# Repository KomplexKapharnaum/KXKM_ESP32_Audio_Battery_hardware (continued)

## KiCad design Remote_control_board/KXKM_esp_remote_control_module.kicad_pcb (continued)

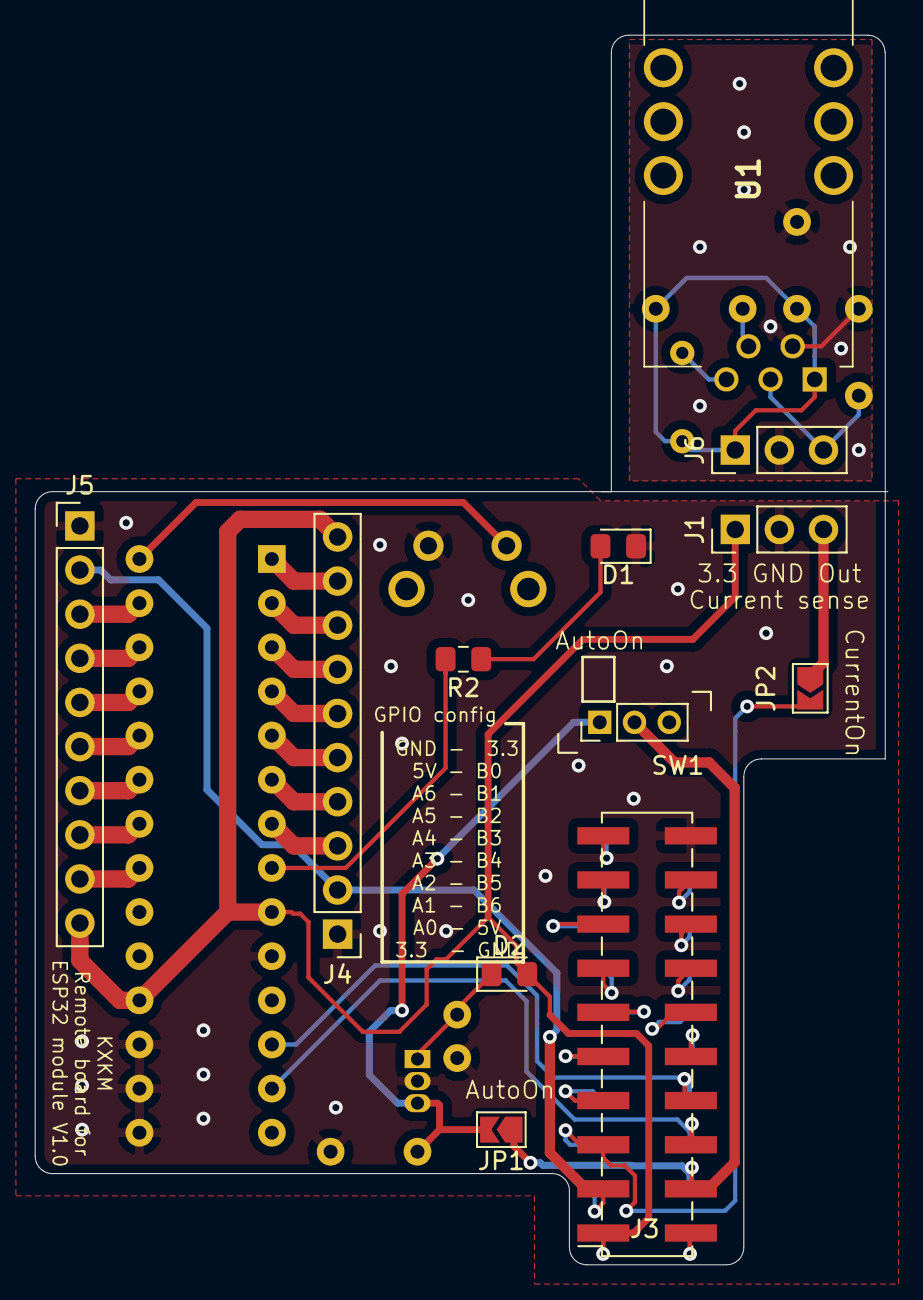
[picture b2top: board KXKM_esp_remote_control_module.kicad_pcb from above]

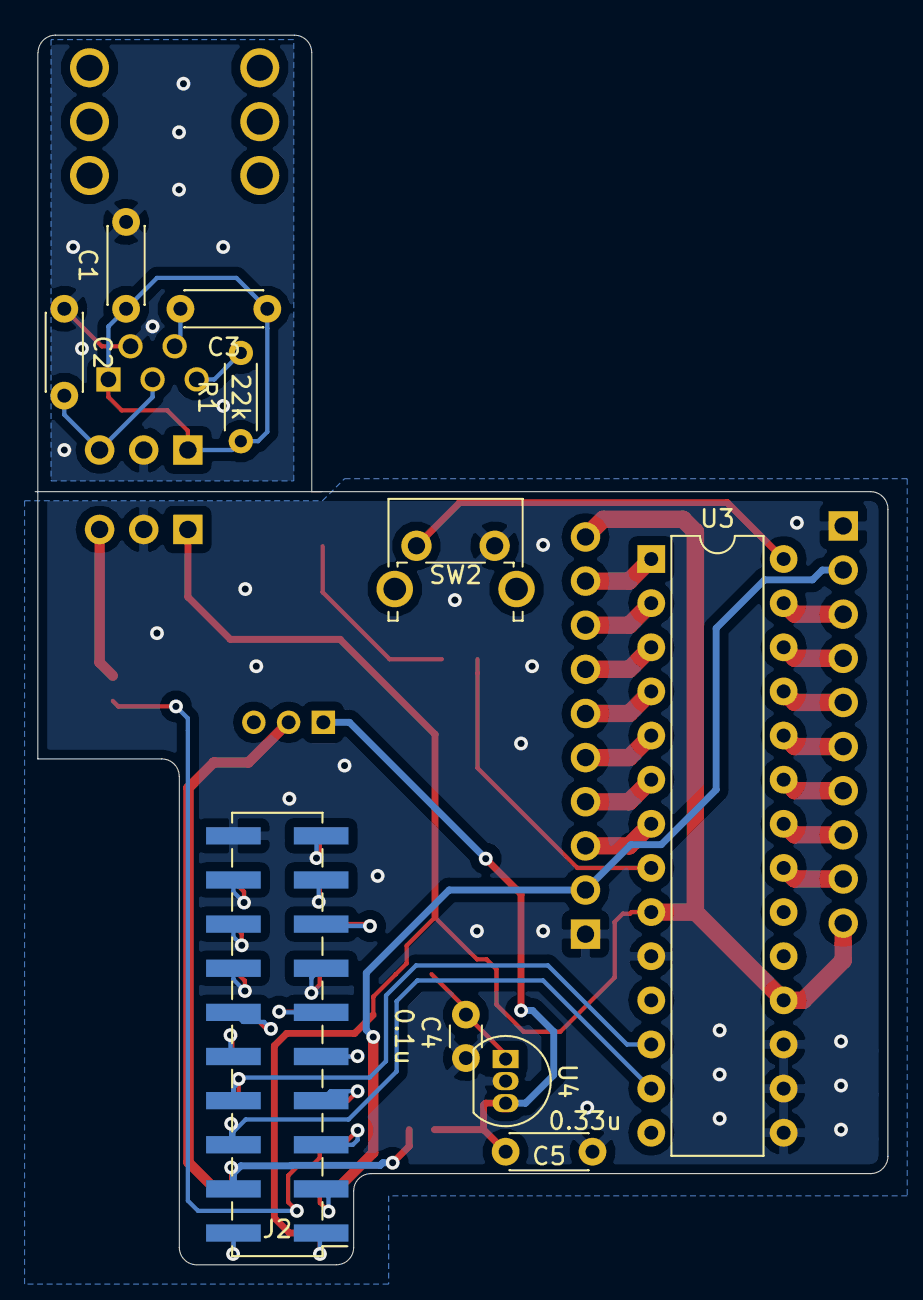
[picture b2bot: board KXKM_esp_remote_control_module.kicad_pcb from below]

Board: 2 copper layers, 48.9 x 70.8 mm, 22 parts (10 on the bottom side), 45 nets.

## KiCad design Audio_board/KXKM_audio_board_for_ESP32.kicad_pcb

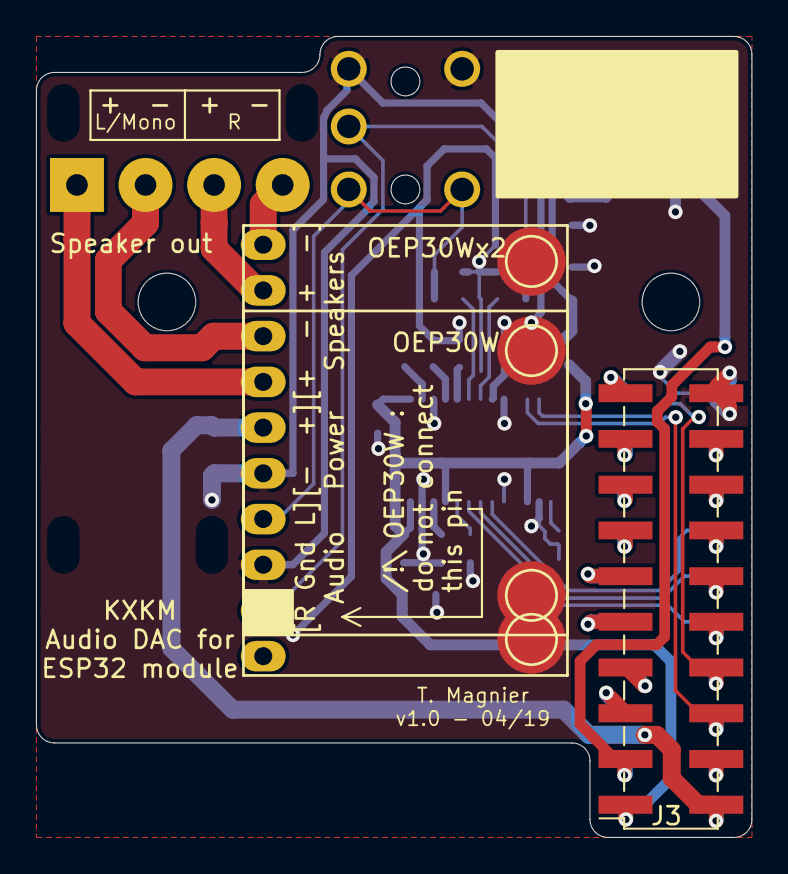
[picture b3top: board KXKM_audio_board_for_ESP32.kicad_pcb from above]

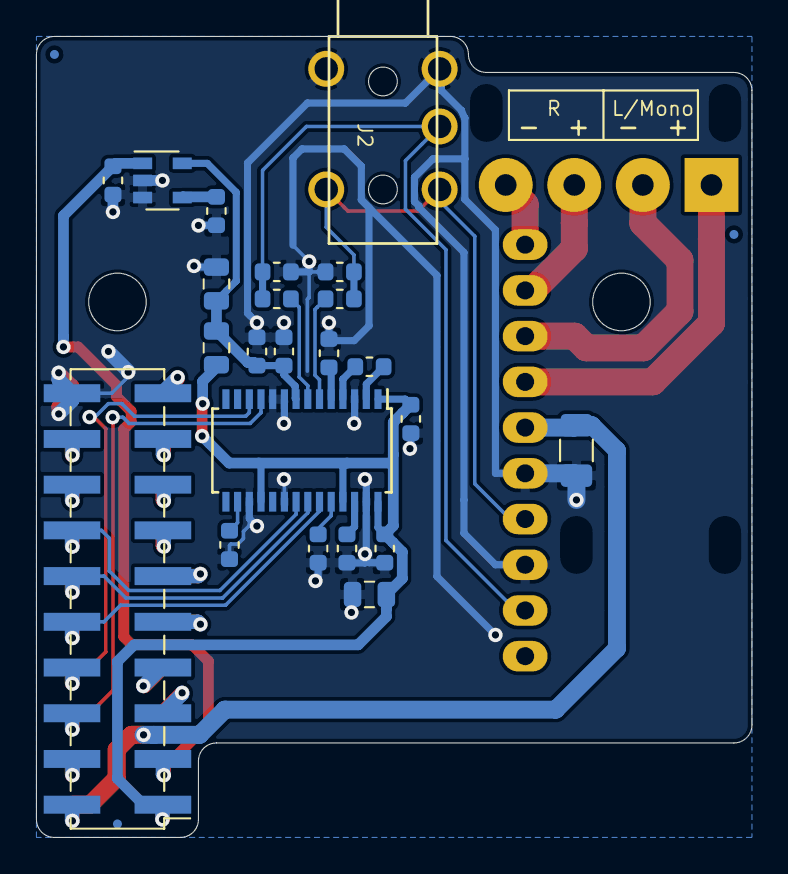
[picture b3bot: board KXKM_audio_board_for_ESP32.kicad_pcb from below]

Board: 2 copper layers, 39.8 x 44.5 mm, 32 parts (26 on the bottom side), 36 nets.

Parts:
C1, C6, C7, C8, C11: 0.1uF; C_0603_1608Metric
C2: 10nF; C_0603_1608Metric
C3, C5: 10uF; C_0805_2012Metric
C4: 1uF; C_0603_1608Metric
C9, C10: 2.2uF/25V; C_0603_1608Metric
C12, C13: 2.2nF/C0G; C_0603_1608Metric
C14: 10uF/50V; C_1206_3216Metric
FB1: Ferrite/60R/3A; L_0805_2012Metric
FID1, FID2, FID3: Fiducial; Fiducial_0.5mm_Mask1mm
H1, H2: MountingHole; MountingHole_3.2mm_M3
J1: Conn_02x10_Odd_Even; PinHeader_2x10_P2.54mm_Vertical_SMD
J2: AudioJack2_Ground; Jack_3.5mm_stereo_PJ-313D
J3: Conn_02x10_Odd_Even; PinSocket_2x10_P2.54mm_Vertical_SMD
J4: Conn_01x04; SolderWirePad_1x04_P3.81mm_Drill1.2mm
R1, R2: 470R/1%; R_0603_1608Metric
R3, R4: 10k; R_0603_1608Metric
U1: DNP/TPS79133DBVR; SOT-23-5
U2: PCM5121; TSSOP-28_4.4x9.7mm_P0.65mm
U3: Audio_amp_OEP30W
U4: Audio_amp_OEP30Wx2

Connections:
+3.3VA: C4.1, C5.1, C7.1, FB1.1, U1.5, U2.8
+3V3: C3.1, C6.1, C8.1, FB1.2, J1.1, J3.1, U2.1, U2.18, U2.25, U2.28
+BATT: J1.4, J3.4
+VSW: C14.1, J1.2, J3.2, U4.5
/ADC: J1.5, J3.5
/Audio/ADDR_1: R3.1, U2.24
/Audio/ADDR_2: R4.1, U2.16
/Audio/AUDIO_L: C13.1, J2.T, R1.1, U4.7
/Audio/AUDIO_R: C12.1, J2.S, R2.1, U4.9
/DMX_DE: J1.15, J3.15
/DMX_DI: J1.17, J3.17
/DMX_RO: J1.19, J3.19
/I2C_SCL: J1.8, J3.8, U2.12
/I2C_SDA: J1.6, J3.6, U2.11
/I2S_BCK: J1.14, J3.14, U2.21
/I2S_DATA: J1.12, J3.12, U2.22
/I2S_LRCK: J1.10, J3.10, U2.23
/LED_D1: J1.16, J3.16
/LED_D2: J1.18, J3.18
/SPI_CS: J1.13, J3.13
/SPI_MISO: J1.9, J3.9
/SPI_MOSI: J1.11, J3.11
/SPI_SCK: J1.7, J3.7
GND: C1.1, C2.1, C3.2, C4.2, C5.2, C6.2, C7.2, C8.2, C10.2, C11.2, C12.2, C13.2, C14.2, J1.20, J2.G, J3.20, R3.2, R4.2, U1.2, U1.3, U2.3, U2.9, U2.10, U2.17, U2.20, U2.27, U3.4, U4.6, U4.8
unnamed: C2.2, U1.4
unnamed: C9.1, U2.2
unnamed: C9.2, U2.4
unnamed: C10.1, U2.5
unnamed: C11.1, U2.26
unnamed: J4.1, U4.4
unnamed: J4.2, U4.3
unnamed: J4.3, U4.2
unnamed: J4.4, U4.1
unnamed: R1.2, U2.6
unnamed: R2.2, U2.7
VBUS: C1.2, J1.3, J3.3, U1.1

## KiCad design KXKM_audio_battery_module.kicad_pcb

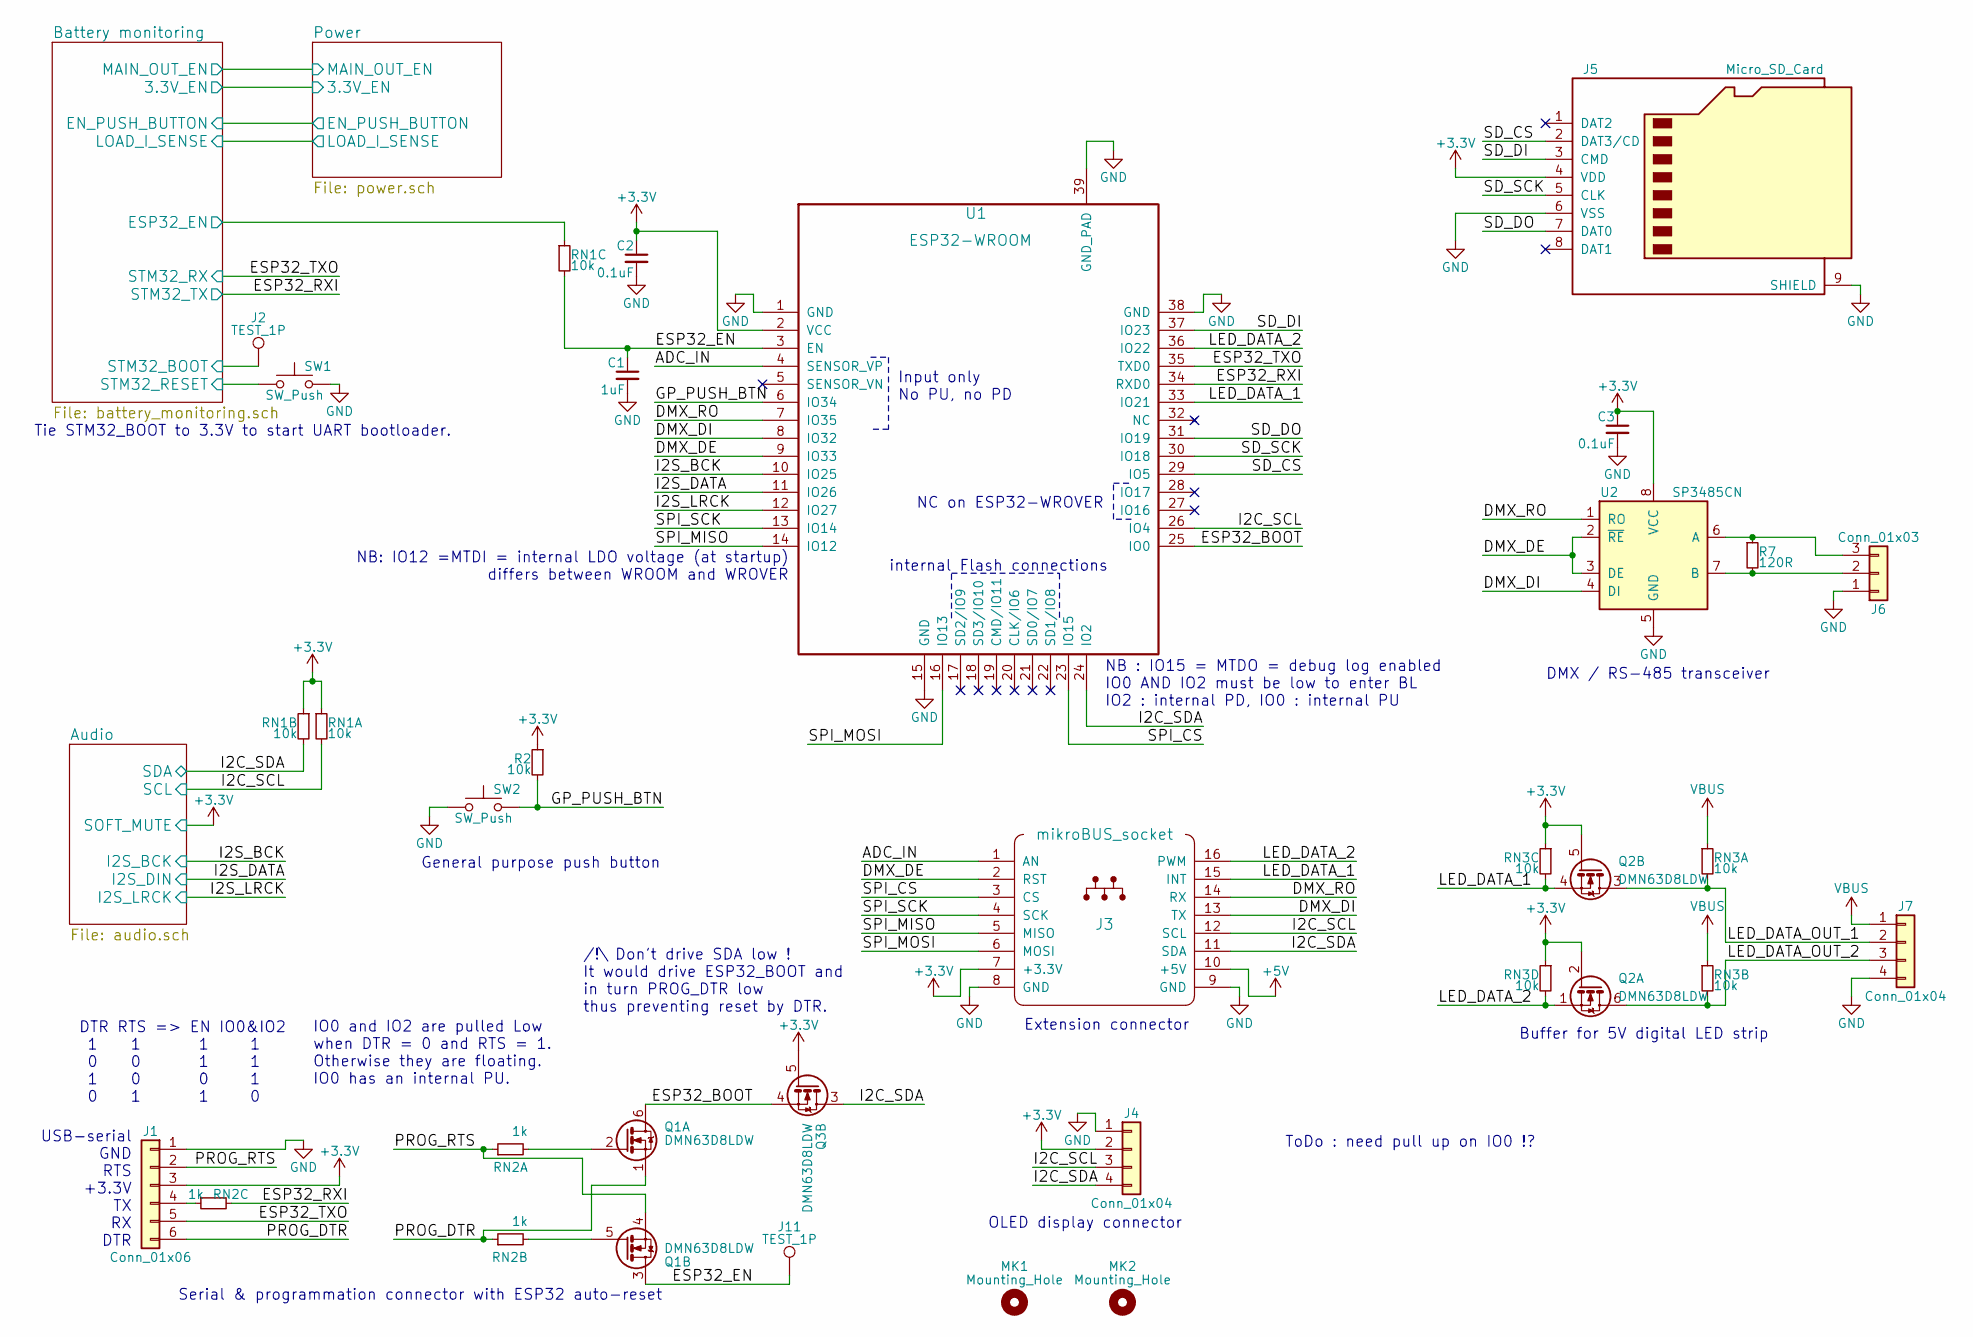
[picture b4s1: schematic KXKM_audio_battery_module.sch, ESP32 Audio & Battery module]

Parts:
C1: 1uF; C_0603
C2, C3: 0.1uF; C_0603
J1: Conn_01x06; Pin_Header_Straight_1x06_Pitch2.54mm
J2, J11: TEST_1P; Test_Point_Pad_d1.5mm
J3: mikroBUS_socket; MIKROBUS_HOST_CONN
J4: Conn_01x04; Pin_Header_Straight_1x04_Pitch2.54mm_SMD_Pin1Left
J5: Micro_SD_Card; microSD-Receptacle-SelfEject
J6: Conn_01x03; Pin_Header_Straight_1x03_Pitch2.54mm
J7: Conn_01x04; Pin_Header_Straight_1x04_Pitch2.54mm
MK1, MK2: Mounting_Hole; MountingHole_3.2mm_M3
Q1, Q2, Q3: DMN63D8LDW; SOT-363_SC-70-6
R2: 10k; R_0603
R7: 120R; R_0603
RN1, RN3: 10k; R_Array_Convex_4x0402
RN2: 1k; R_Array_Convex_4x0402
SW1, SW2: SW_Push; SW_SPST_KMR2
U1: ESP32-WROOM; ESP32-WROOM_WROVER
U2: SP3485CN; SOIC-8_3.9x4.9mm_Pitch1.27mm

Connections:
+3V3: C2.1, C3.1, J1.3, J3.7 (+3.3V), J4.2, J5.4 (VDD), Q2.2 (G), Q2.5 (G), Q3.5 (G), R2.1, RN1.1, RN1.2, RN3.3, RN3.4, U1.2 (VCC), U2.8 (VCC); also elsewhere on the board
+5V: J3.10 (+5V); also elsewhere on the board
/ADC_IN: J3.1 (AN), U1.4 (SENSOR_VP)
/Battery monitoring/ESP32_EN: RN1.3; also elsewhere on the board
/Battery monitoring/STM32_BOOT: J2.1; also elsewhere on the board
/Battery monitoring/STM32_RESET: SW1.1; also elsewhere on the board
/DMX_DE: J3.2 (RST), U1.9 (IO33), U2.2 (~RE~), U2.3 (DE)
/DMX_DI: J3.13 (TX), U1.8 (IO32), U2.4 (DI)
/DMX_RO: J3.14 (RX), U1.7 (IO35), U2.1 (RO)
/ESP32_BOOT: Q1.6 (D), Q3.4 (S), U1.25 (IO0)
/ESP32_EN: C1.1, J11.1, Q1.3 (D), RN1.6, U1.3 (EN)
/ESP32_RXI: RN2.6, U1.34 (RXD0); also elsewhere on the board
/ESP32_TXO: J1.5, U1.35 (TXD0); also elsewhere on the board
/GP_PUSH_BTN: R2.2, SW2.2, U1.6 (IO34)
/I2C_SCL: J3.12 (SCL), J4.3, RN1.8, U1.26 (IO4); also elsewhere on the board
/I2C_SDA: J3.11 (SDA), J4.4, Q3.3 (D), RN1.7, U1.24 (IO2); also elsewhere on the board
/I2S_BCK: U1.10 (IO25); also elsewhere on the board
/I2S_DATA: U1.11 (IO26); also elsewhere on the board
/I2S_LRCK: U1.12 (IO27); also elsewhere on the board
/LED_DATA_1: J3.15 (INT), Q2.4 (S), RN3.6, U1.33 (IO21)
/LED_DATA_2: J3.16 (PWM), Q2.1 (S), RN3.5, U1.36 (IO22)
/LED_DATA_OUT_1: J7.2, Q2.3 (D), RN3.8
/LED_DATA_OUT_2: J7.3, Q2.6 (D), RN3.7
/PROG_DTR: J1.6, Q1.1 (S), RN2.2
/PROG_RTS: J1.2, Q1.4 (S), RN2.1
/SD_CS: J5.2 (DAT3/CD), U1.29 (IO5)
/SD_DI: J5.3 (CMD), U1.37 (IO23)
/SD_DO: J5.7 (DAT0), U1.31 (IO19)
/SD_SCK: J5.5 (CLK), U1.30 (IO18)
/SPI_CS: J3.3 (CS), U1.23 (IO15)
/SPI_MISO: J3.5 (MISO), U1.14 (IO12)
/SPI_MOSI: J3.6 (MOSI), U1.16 (IO13)
/SPI_SCK: J3.4 (SCK), U1.13 (IO14)
GND: C1.2, C2.2, C3.2, J1.1, J3.8 (GND), J3.9 (GND), J4.1, J5.6 (VSS), J5.9 (SHIELD), J6.1, J7.4, SW1.2, SW2.1, U1.1 (GND), U1.15 (GND), U1.38 (GND), U1.39 (GND_PAD), U2.5 (GND); also elsewhere on the board
unnamed: J1.4, RN2.3
unnamed: J6.2, R7.2, U2.7 (B)
unnamed: J6.3, R7.1, U2.6 (A)
unnamed: Q1.2 (G), RN2.8
unnamed: Q1.5 (G), RN2.7
VBUS: J7.1, RN3.1, RN3.2; also elsewhere on the board

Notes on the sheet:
NC on ESP32-WROVER
internal Flash connections
NB: IO12 =MTDI = internal LDO voltage (at startup) differs between WROOM and WROVER
NB : IO15 = MTDO = debug log enabled IO0 AND IO2 must be low to enter BL IO2 : internal PD, IO0 : internal PU
DMX / RS-485 transceiver
Extension connector
OLED display connector
Tie STM32_BOOT to 3.3V to start UART bootloader.
Serial & programmation connector with ESP32 auto-reset
USB-serial GND RTS +3.3V TX RX DTR
Buffer for 5V digital LED strip
Input only No PU, no PD
DTR RTS => EN IO0&IO2 1 1 1 1 0 0 1 1 1 0 0 1 0 1 1 0
ToDo : need pull up on IO0 !?
General purpose push button
IO0 and IO2 are pulled Low when DTR = 0 and RTS = 1. Otherwise they are floating. IO0 has an internal PU.
/!\ Don't drive SDA low ! It would drive ESP32_BOOT and in turn PROG_DTR low thus preventing reset by DTR.

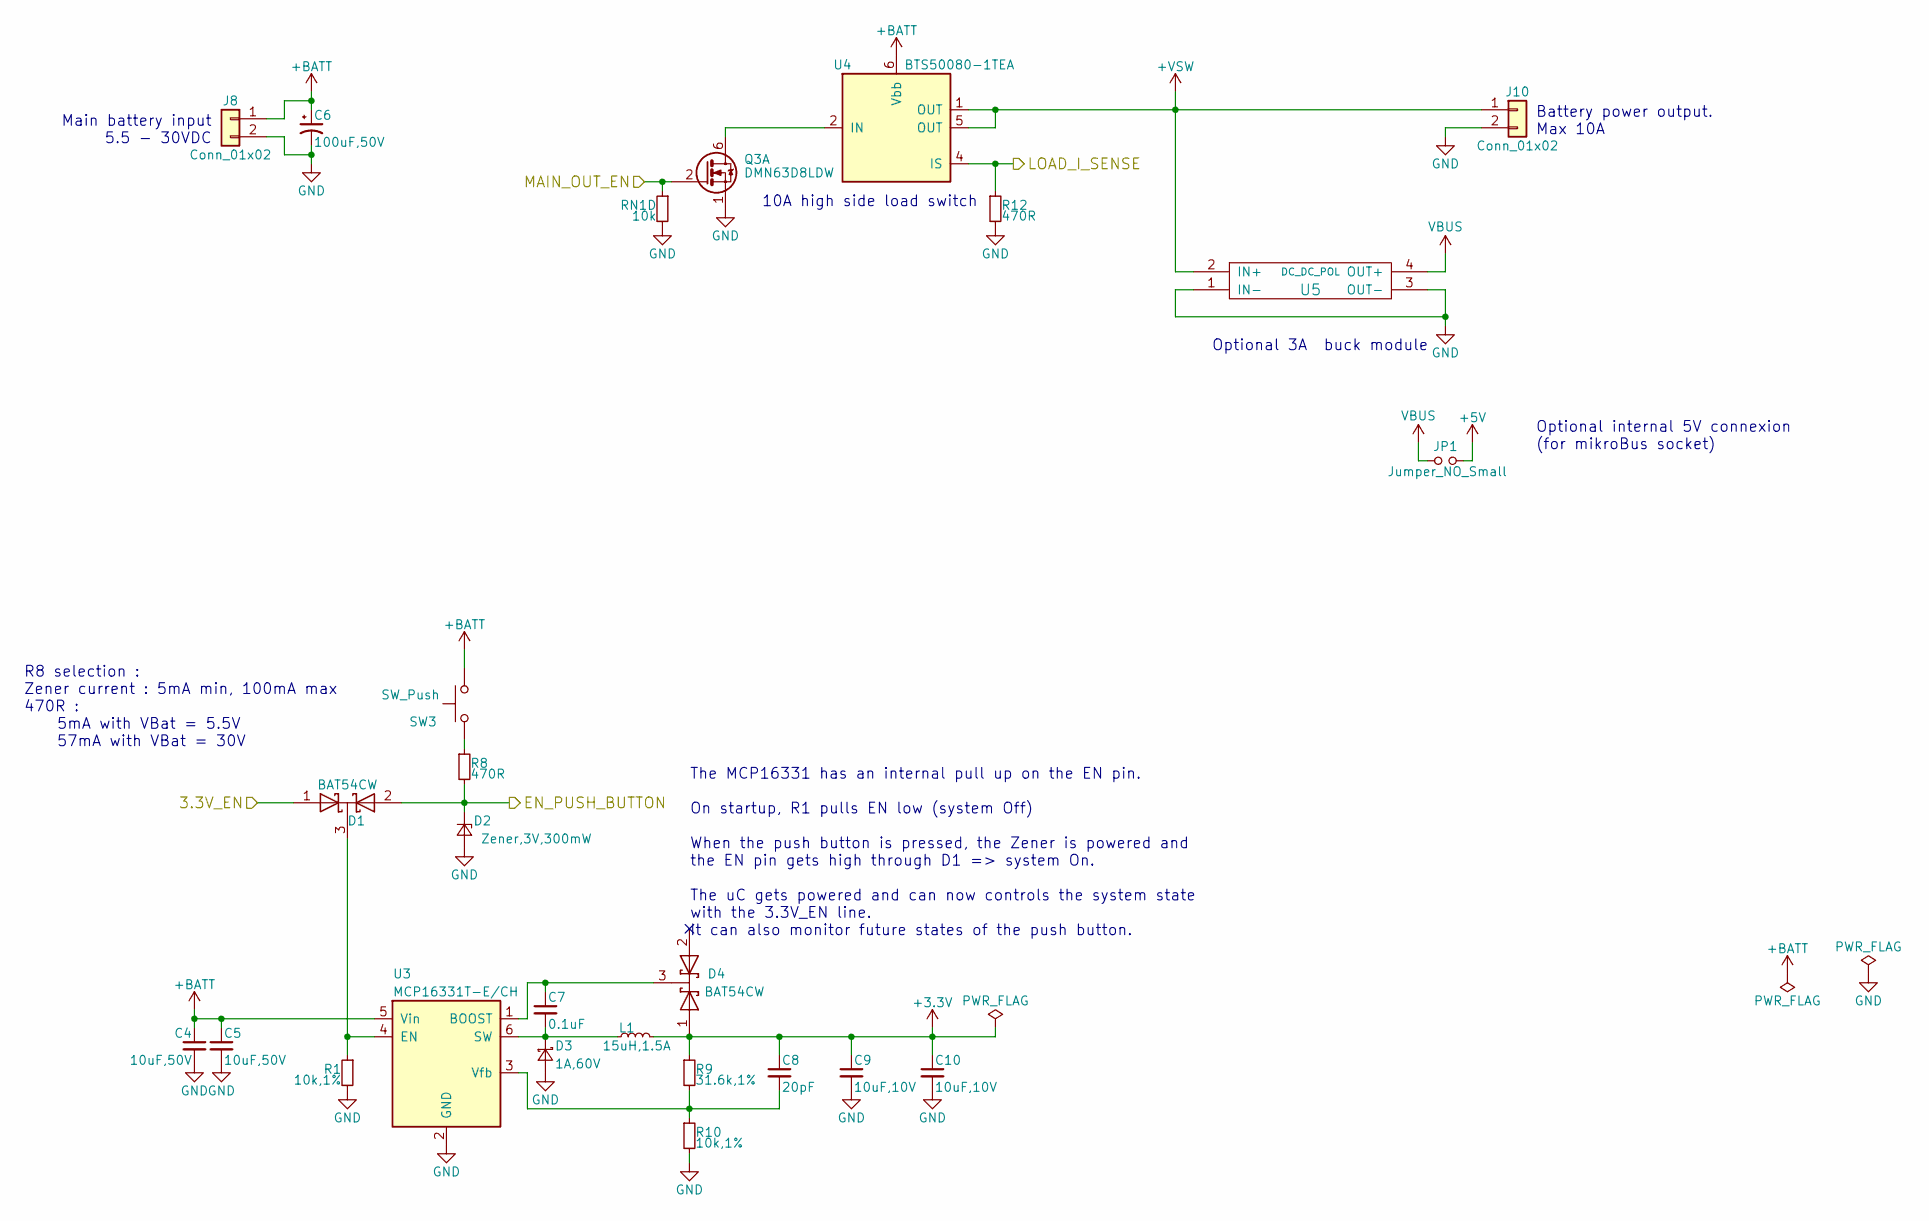
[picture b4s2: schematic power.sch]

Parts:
C4, C5: 10uF,50V; C_1206
C6: 100uF,50V; CP_Elec_8x10
C7: 0.1uF; C_0603
C8: 20pF; C_0603
C9, C10: 10uF,10V; C_0805
D1, D4: BAT54CW; SOT-323_SC-70
D2: Zener,3V,300mW; D_SOD-323
D3: 1A,60V; D_SOD-123F
J8, J10: Conn_01x02; TerminalBlock_Pheonix_PT-3.5mm_2pol
JP1: Jumper_NO_Small; Solder_Jumper_2_open
L1: 15uH,1.5A; L_7.3x7.3_H4.5
Q3: DMN63D8LDW; SOT-363_SC-70-6
R1, R10: 10k,1%; R_0603
R8, R12: 470R; R_0603
R9: 31.6k,1%; R_0603
RN1: 10k; R_Array_Convex_4x0402
SW3: SW_Push; SW_Tactile_SPST_Angled_PTS645Vx58-2LFS_horiz_pads
U3: MCP16331T-E/CH; SOT-23-6
U4: BTS50080-1TEA; TO-252-5_TabPin6
U5: DC_DC_POL; DC_DC_buck_module_Mini360

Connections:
+3V3: C8.1, C9.1, C10.1, D4.1 (A), L1.2, R9.1; also elsewhere on the board
+5V: JP1.2; also elsewhere on the board
+BATT: C4.1, C5.1, C6.1, J8.1, SW3.2, U3.5 (Vin), U4.6 (Vbb); also elsewhere on the board
+VSW: J10.1, U4.1 (OUT), U4.5 (OUT), U5.2 (IN+); also elsewhere on the board
/Battery monitoring/3.3V_EN: D1.1 (A); also elsewhere on the board
/Battery monitoring/EN_PUSH_BUTTON: D1.2 (A), D2.1 (K), R8.2; also elsewhere on the board
/Battery monitoring/LOAD_I_SENSE: R12.1, U4.4 (IS); also elsewhere on the board
/Battery monitoring/MAIN_OUT_EN: Q3.2 (G), RN1.4; also elsewhere on the board
GND: C4.2, C5.2, C6.2, C9.2, C10.2, D2.2 (A), D3.2 (A), J8.2, J10.2, Q3.1 (S), R1.2, R10.2, R12.2, RN1.5, U3.2 (GND), U5.1 (IN-), U5.3 (OUT-); also elsewhere on the board
unnamed: C7.1, D4.3 (K), U3.1 (BOOST)
unnamed: C7.2, D3.1 (K), L1.1, U3.6 (SW)
unnamed: C8.2, R9.2, R10.1, U3.3 (Vfb)
unnamed: D1.3 (K), R1.1, U3.4 (EN)
unnamed: Q3.6 (D), U4.2 (IN)
unnamed: R8.1, SW3.1
VBUS: JP1.1, U5.4 (OUT+); also elsewhere on the board

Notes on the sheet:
Main battery input 5.5 - 30VDC
Battery power output. Max 10A
Optional 3A buck module
The MCP16331 has an internal pull up on the EN pin. On startup, R1 pulls EN low (system Off) When the push button is pressed, the Zener is powered and the EN pin gets high through D1 => system On. The uC gets powered and can now controls the system state with the 3.3V_EN line. It can also monitor f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
10A high side load switch
Optional internal 5V connexion (for mikroBus socket)
R8 selection : Zener current : 5mA min, 100mA max 470R : 5mA with VBat = 5.5V 57mA with VBat = 30V

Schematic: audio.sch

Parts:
C11: 10uF 10V; C_0805
C12: 1uF; C_0603
C13, C14, C15, C18: 0.1uF; C_0603
C16, C17: 2.2uF 25V; C_0603
C19, C20: 2.2nF; C_0603
C25: 10uF 50V; C_1206
J9: Conn_01x05; Socket_Strip_Straight_1x05_Pitch2.54mm
J12: Audio-Jack-3; Jack_3.5mm_stereo_PJ-313D
J13: Conn_01x05
J14: Conn_01x10
J15: Conn_01x07
R13, R14: 470R; R_0603
U6: PCM5141; TSSOP-28_4.4x9.7mm_Pitch0.65mm

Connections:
+3V3: C11.1, C12.1, C13.1, C14.1, C15.1, U6.1 (CPVDD), U6.8 (AVDD), U6.18 (MODE2/MS), U6.25 (XSMT), U6.28 (DVDD); also elsewhere on the board
+VSW: C25.1, J9.1; also elsewhere on the board
/Audio/AUDIO_L: C20.1, J9.3, J12.1, J13.3, R13.1
/Audio/AUDIO_R: C19.1, J9.5, J12.2, J13.5, R14.1
/I2C_SCL: U6.12 (SCL/MC/ATT1); also elsewhere on the board
/I2C_SDA: U6.11 (SDA/MOSI/ATT2); also elsewhere on the board
/I2S_BCK: U6.21 (BCK); also elsewhere on the board
/I2S_DATA: U6.22 (DIN); also elsewhere on the board
/I2S_LRCK: U6.23 (LRCK); also elsewhere on the board
GND: C11.2, C12.2, C13.2, C14.2, C15.2, C17.2, C18.2, C19.2, C20.2, C25.2, J9.2, J9.4, J12.3, U6.3 (CPGND), U6.9 (AGND), U6.10 (VCOM/DEMP), U6.16 (ADR2/GPIO2/DOUT), U6.17 (MODE1), U6.20 (SCK), U6.24 (ADR1/MISO/GPIO1/FMT), U6.27 (DGND); also elsewhere on the board
unnamed: C16.1, U6.2 (CAPP)
unnamed: C16.2, U6.4 (CAPM)
unnamed: C17.1, U6.5 (VNEG)
unnamed: C18.1, U6.26 (LDOO)
unnamed: R13.2, U6.6 (OUTL)
unnamed: R14.2, U6.7 (OUTR)

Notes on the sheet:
Using I2C mode : MODE1 = L ; MODE2 = H 7-bit I2C address : 0x4C (ADR1 = ADR2 = 0)
Mini-jack Line out 2VRMS
I2S interface (3-Wire)
I2C interface
OEP30Wx2
OEP30W
PCB
Power amp module connector

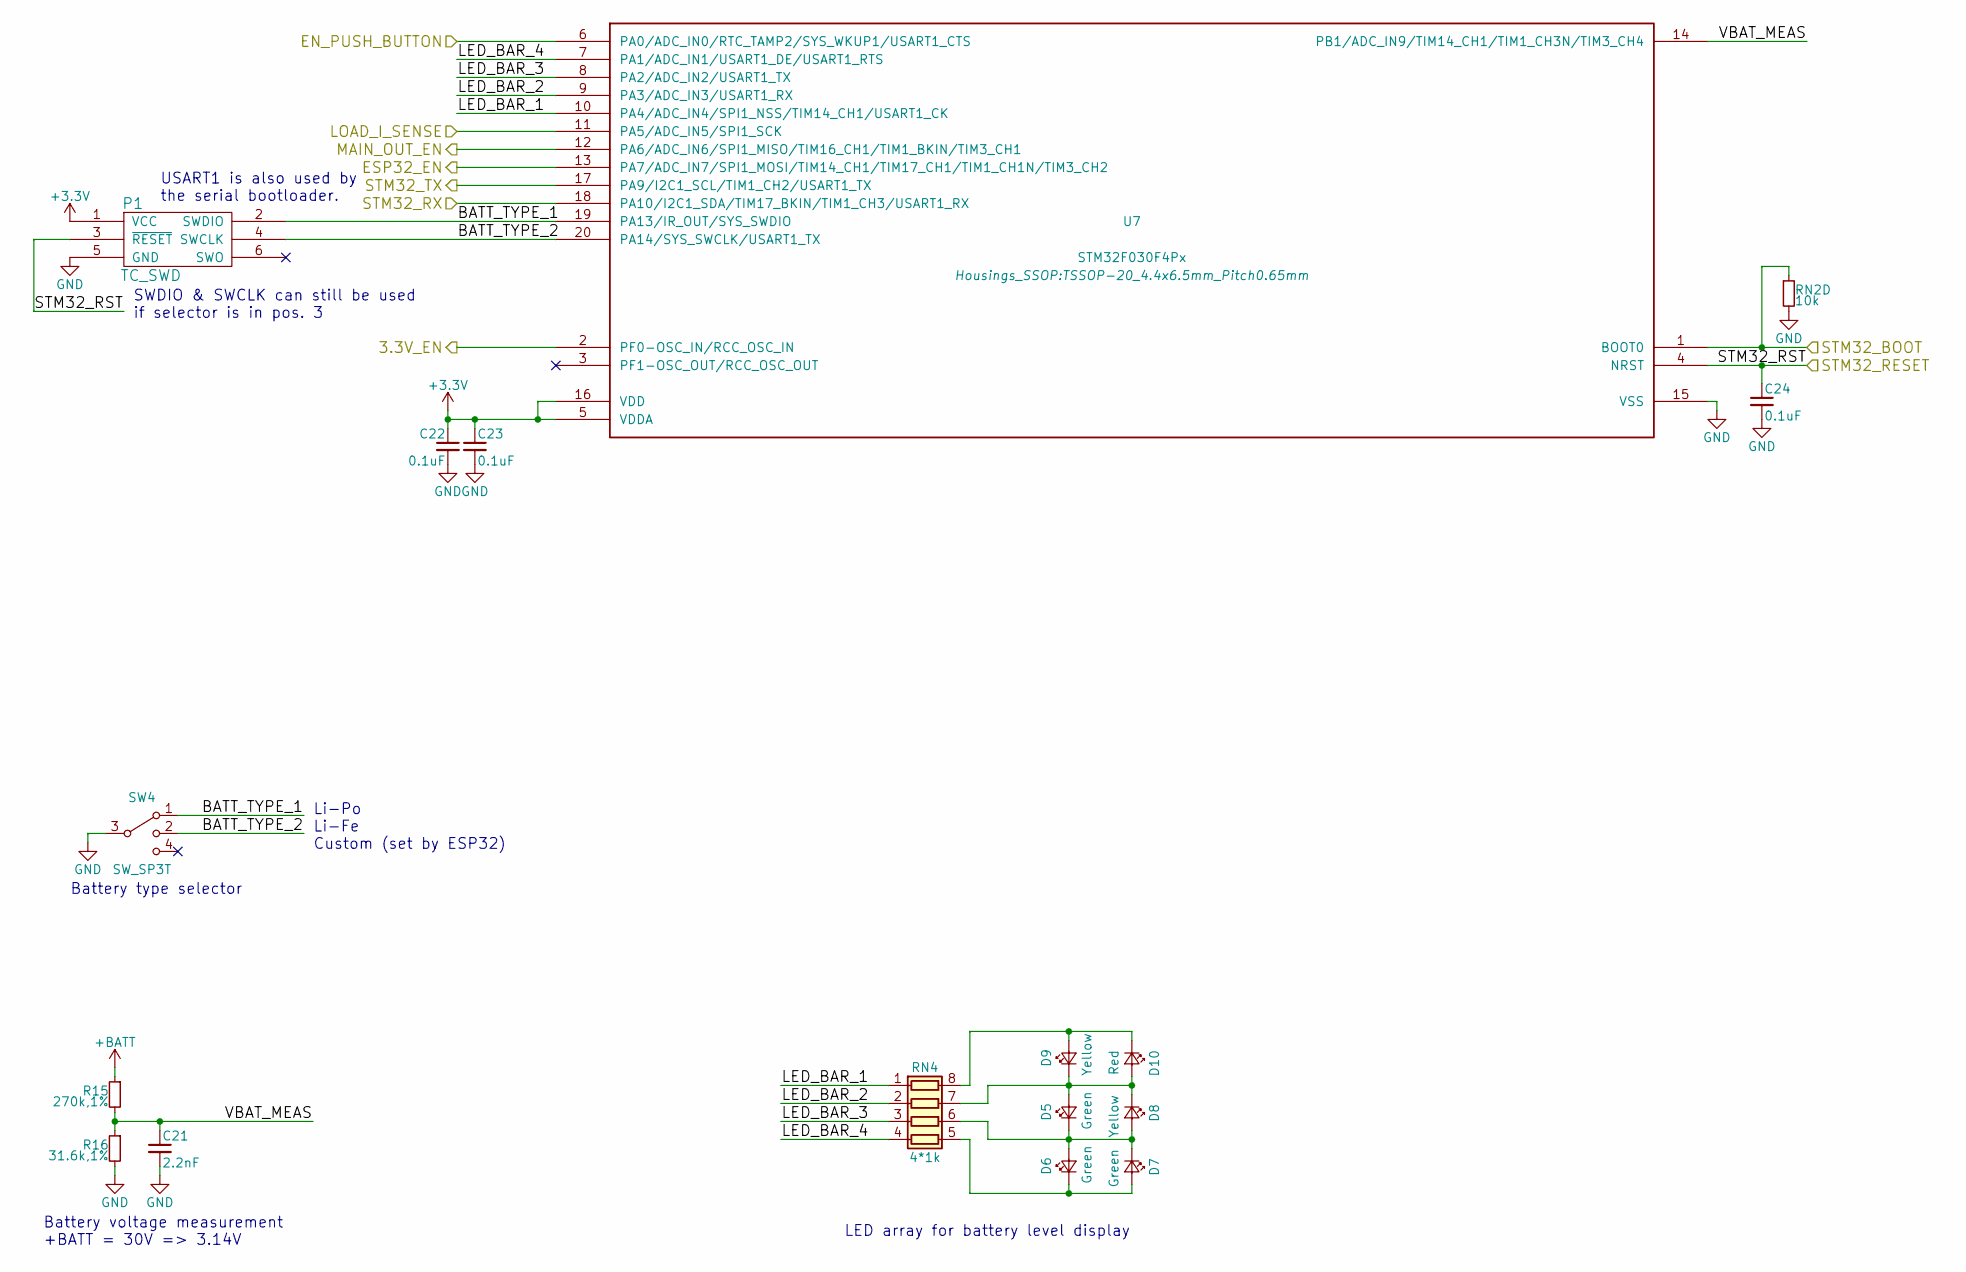
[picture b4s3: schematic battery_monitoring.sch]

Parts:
C21: 2.2nF; C_0603
C22, C23, C24: 0.1uF; C_0603
D5, D6, D7: Green; LED_0603
D8, D9: Yellow; LED_0603
D10: Red; LED_0603
P1: TC_SWD; Tag-Connect_TC2030-IDC-NL
R15: 270k,1%; R_0603
R16: 31.6k,1%; R_0603
RN2: 10k; R_Array_Convex_4x0402
RN4: 4*1k; R_Array_Convex_4x0402
SW4: SW_SP3T; SW_SP3T_PCM13
U7: STM32F030F4Px; TSSOP-20_4.4x6.5mm_Pitch0.65mm

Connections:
+3V3: C22.1, C23.1, P1.1 (VCC), U7.5 (VDDA), U7.16 (VDD); also elsewhere on the board
+BATT: R15.1; also elsewhere on the board
/Battery monitoring/3.3V_EN: U7.2 (PF0-OSC_IN/RCC_OSC_IN); also elsewhere on the board
/Battery monitoring/BATT_TYPE_1: P1.2 (SWDIO), SW4.1, U7.19 (PA13/IR_OUT/SYS_SWDIO)
/Battery monitoring/BATT_TYPE_2: P1.4 (SWCLK), SW4.2, U7.20 (PA14/SYS_SWCLK/USART1_TX)
/Battery monitoring/EN_PUSH_BUTTON: U7.6 (PA0/ADC_IN0/RTC_TAMP2/SYS_WKUP1/USART1_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); also elsewhere on the board
/Battery monitoring/ESP32_EN: U7.13 (PA7/ADC_IN7/SPI1_MOSI/TIM14_CH1/TIM17_C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); also elsewhere on the board
/Battery monitoring/LED_BAR_1: RN4.1 (R1.1), U7.10 (PA4/ADC_IN4/SPI1_NSS/TIM14_CH1/USART1_CK)
/Battery monitoring/LED_BAR_2: RN4.2 (R2.1), U7.9 (PA3/ADC_IN3/USART1_RX)
/Battery monitoring/LED_BAR_3: RN4.3 (R3.1), U7.8 (PA2/ADC_IN2/USART1_TX)
/Battery monitoring/LED_BAR_4: RN4.4 (R4.1), U7.7 (PA1/ADC_IN1/USART1_DE/USART1_RTS)
/Battery monitoring/LOAD_I_SENSE: U7.11 (PA5/ADC_IN5/SPI1_SCK); also elsewhere on the board
/Battery monitoring/MAIN_OUT_EN: U7.12 (PA6/ADC_IN6/SPI1_MISO/TIM16_CH1/TIM1_BK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); also elsewhere on the board
/Battery monitoring/STM32_BOOT: RN2.4, U7.1 (BOOT0); also elsewhere on the board
/Battery monitoring/STM32_RESET: C24.1, P1.3 (~RESET), U7.4 (NRST); also elsewhere on the board
/Battery monitoring/VBAT_MEAS: C21.1, R15.2, R16.1, U7.14 (PB1/ADC_IN9/TIM14_CH1/TIM1_CH3N/TIM3_CH4)
/ESP32_RXI: U7.17 (PA9/I2C1_SCL/TIM1_CH2/USART1_TX); also elsewhere on the board
/ESP32_TXO: U7.18 (PA10/I2C1_SDA/TIM17_BKIN/TIM1_CH3/USART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); also elsewhere on the board
GND: C21.2, C22.2, C23.2, C24.2, P1.5 (GND), R16.2, RN2.5, SW4.3, U7.15 (VSS); also elsewhere on the board
unnamed: D5.1 (K), D6.2 (A), D7.1 (K), D8.2 (A), RN4.6 (R3.2)
unnamed: D6.1 (K), D7.2 (A), RN4.5 (R4.2)
unnamed: D9.2 (A), D10.1 (K), RN4.8 (R1.2)
unnamed: D5.2 (A), D8.1 (K), D9.1 (K), D10.2 (A), RN4.7 (R2.2)

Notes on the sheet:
Battery type selector
USART1 is also used by the serial bootloader.
Battery voltage measurement +BATT = 30V => 3.14V
LED array for battery level display
SWDIO & SWCLK can still be used if selector is in pos. 3
Li-Po Li-Fe Custom (set by ESP32)

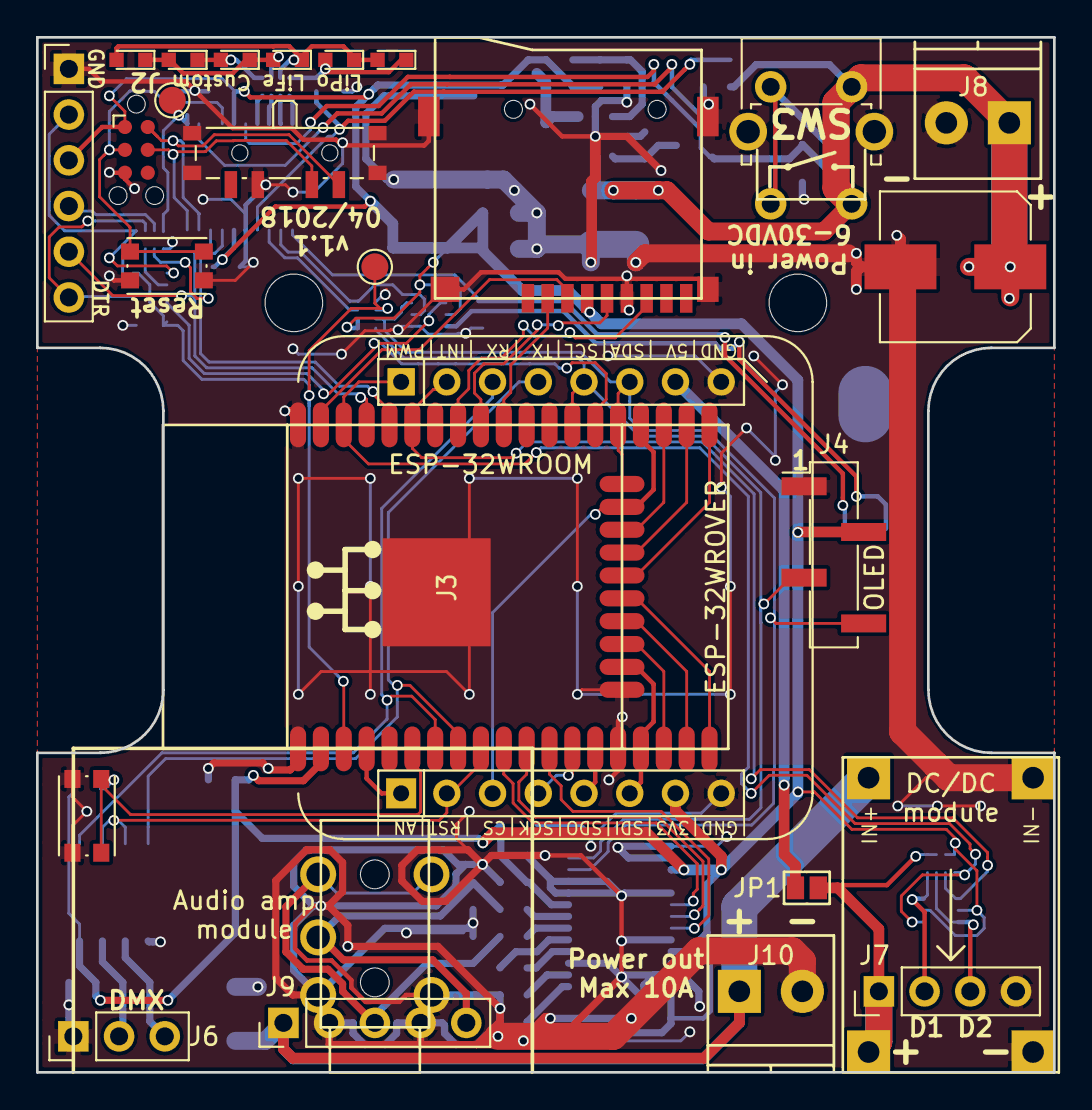
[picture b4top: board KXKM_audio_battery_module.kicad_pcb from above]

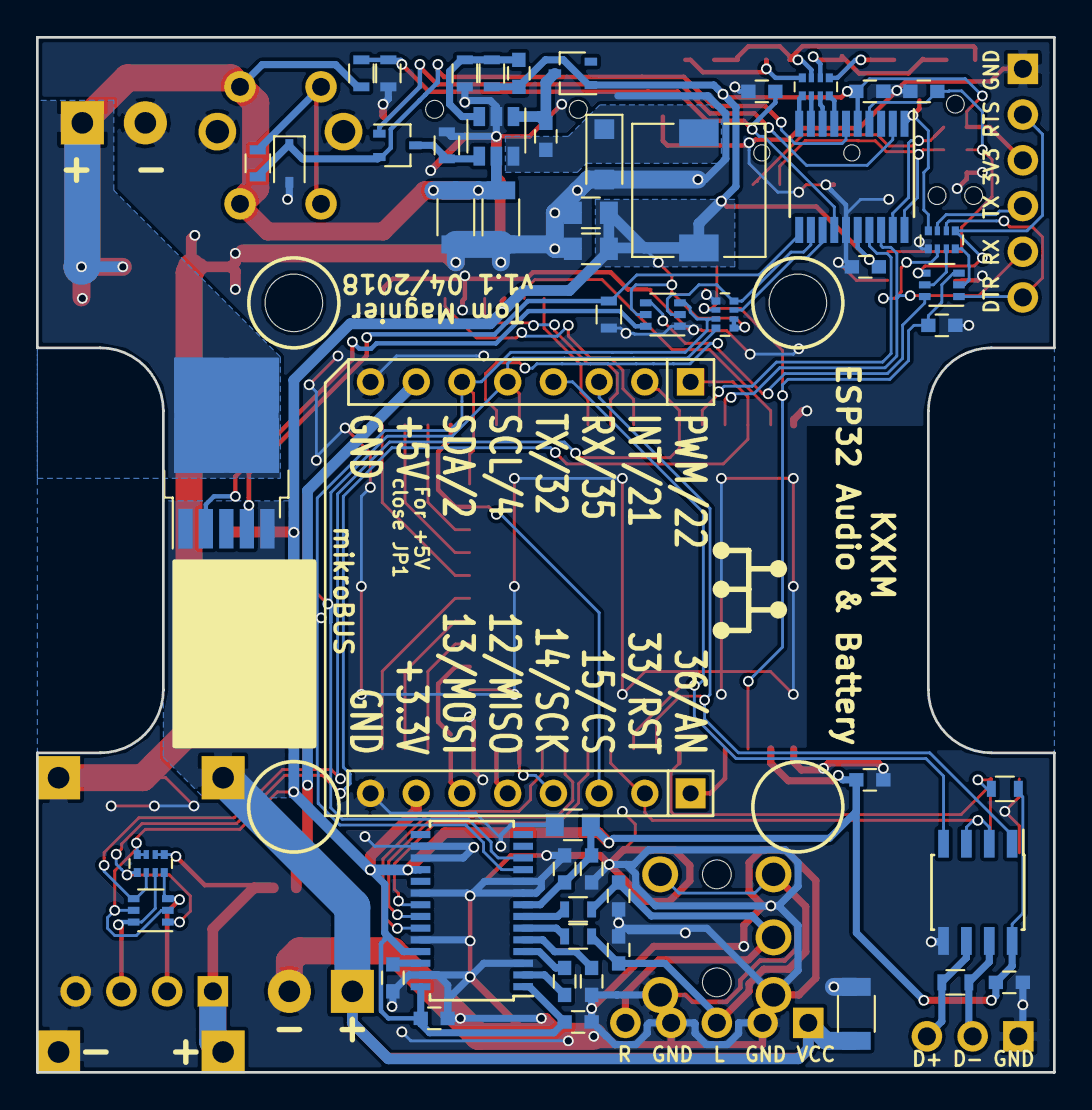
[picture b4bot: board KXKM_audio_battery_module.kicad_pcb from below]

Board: 2 copper layers, 56.5 x 57.5 mm, 81 parts (52 on the bottom side), 71 nets.

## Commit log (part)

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2018-03-09 Initial commit - Schematic and footprint association done, sub modules routed
2018-03-12 Component placement WIP - multiple Hammond enclosures drawn
2018-03-13 Almost all components placed... Saving before mirroring everything
2018-03-23 v1.0 Add 3D files with Hammond enclosures fabrication outputs
2018-03-29 Update PDF schematic
2018-03-30 v1.1 - changed some resistor values ; manufacturability improvements (thermal relief) ; added a test point for ESP32_EN
2018-03-30 Update BOM & fab files
2018-04-19 Final fabrication files for v1.1
2018-10-30 Add checklist and module position files
2018-10-30 Open project with KiCAD v5.0
2019-04-16 v2.0 - audio circuitry on a separate board ; optimized connectors and lots of improvements
2019-04-16 Repository cleanup and add audio board project files
2019-04-18 Fix older symbols assignation
2019-04-18 Fix component values > pick n place convention
2020-02-26 Add Remote control board
2020-02-26 Add Gerbers
2020-02-26 Add Bill Of Material
2020-05-26 update gerber and add current sensor doc
2021-04-30 Documentation output & JLCPCB BoM
2021-04-30 First look at v3 : components on top side only. Board area maximised for
2021-08-26 cleaning and moving components
2021-08-26 update from schematic
2021-08-26 rescue from cache
2021-09-03 update, etc
2021-09-08 passing drc
2021-09-13 pre v3.0 clean
2021-09-13 clean pre v3.0
2021-09-13 clean pre v3.0 - Del gerbers
2021-09-13 releasing v3.0
2021-09-16 doc v3.0
2021-09-16 original BoM JLCSMT
2021-09-16 remove not mounted cmp
2021-09-16 remplace usb and J5
2021-09-27 updating pcb
2021-09-27 v3.1;
2021-09-27 follow up of v3.0 to v3.1, no differences (PCB only
2021-09-27 fix silkscreen and version on silk
2022-01-17 kicad6
2022-07-11 mise en panel
2022-07-11 adding backups
2022-07-11 Rangement BaseBoard par version
2022-07-11 cleanup
2023-06-27 v1 schematic
2023-09-07 update v3.2
    - connecteur XT60 coudé (et disponible chez JLCPCB)
    - modification de l’autoboot pour un redémarrage en cas de perte brêve d’alimentation,
    - ajout de l’empreinte pour rajouter une lecteur microSD
    - mise à jour des piste de sortie batterie conforme pour 10A
    - suppression des pin I2C (déjà dispo sur le GPIO)
    - connecteur JST B3B-EH pour un câblage et éviter les soudure qui casse sur les sortie pour LED
2023-09-07 add freecad file
    add freecad file for casing with cut for CNC
2023-09-07 update casing
    better file naming
2023-10-11 update to v3.2 and casing 3D View
2024-07-04 board in 3.2
2024-09-27 last order
